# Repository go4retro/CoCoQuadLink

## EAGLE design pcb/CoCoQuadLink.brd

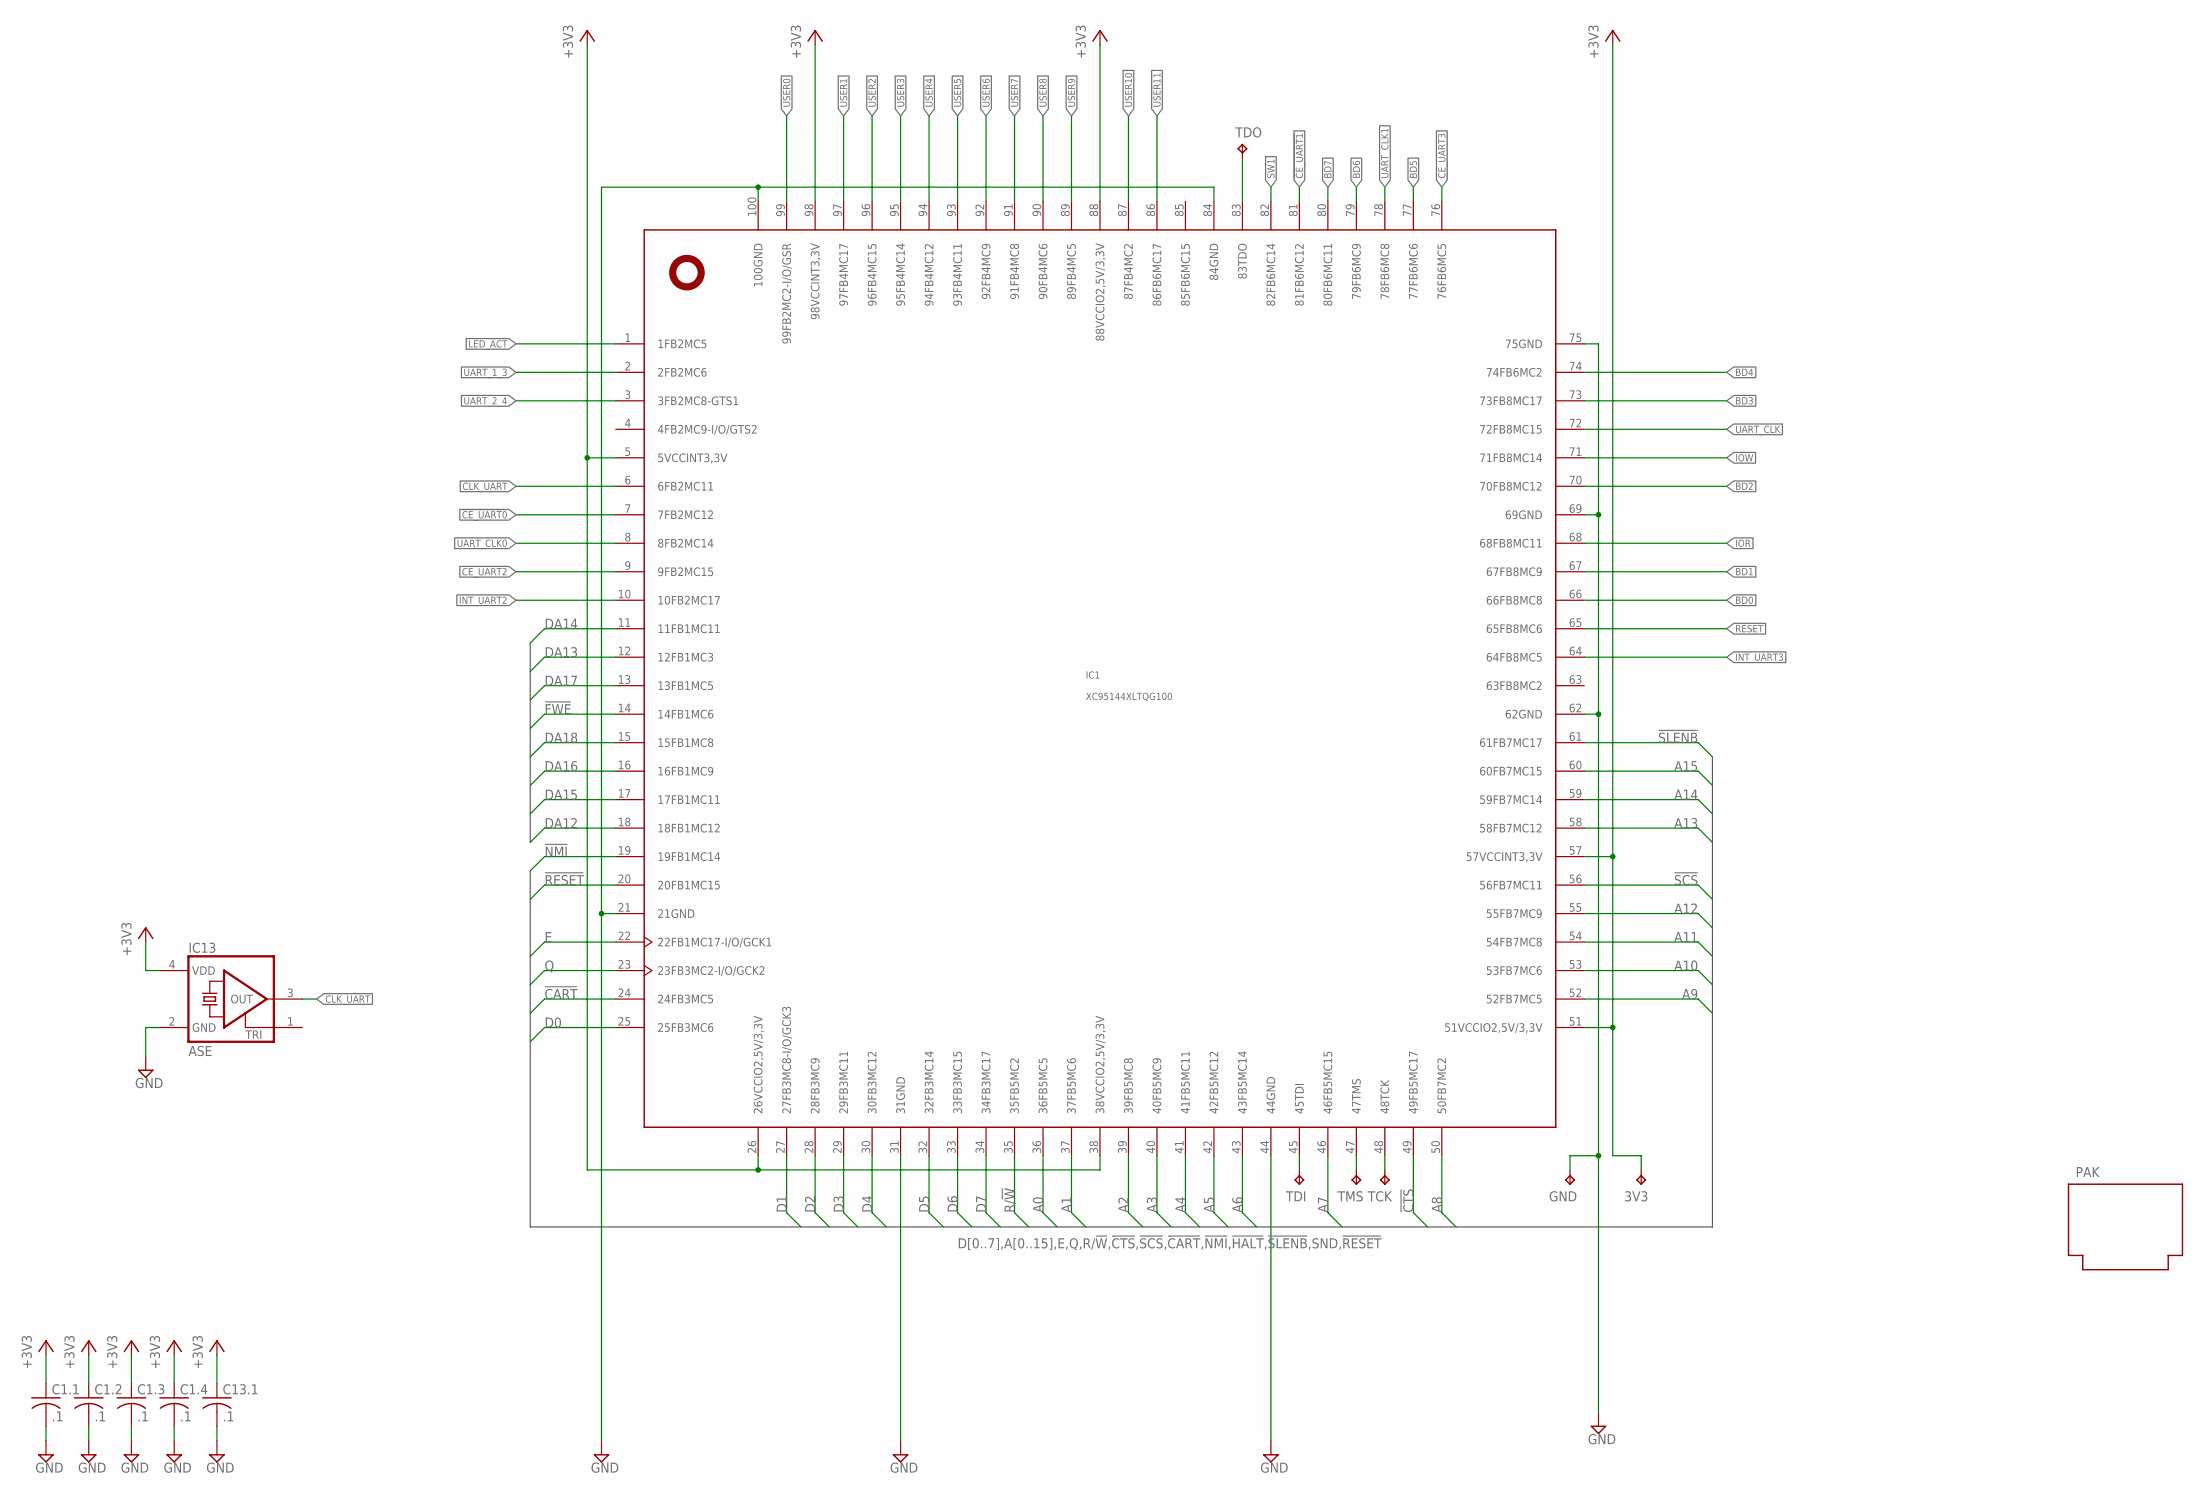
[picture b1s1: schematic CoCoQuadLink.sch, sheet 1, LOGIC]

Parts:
3V3: TPTP10R; TP10R
C1.1, C1.2, C1.3, C1.4, C13.1: .1; C0402
GND: TPTP10R; TP10R
IC1: XC95144XLTQG100; TQFP100
IC13: ASE
PAK: PROGRAM_PAK
TCK: TPTP10R; TP10R
TDI: TPTP10R; TP10R
TDO: TPTP10R; TP10R
TMS: TPTP10R; TP10R

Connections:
!CART: IC1.24 (24FB3MC5); also elsewhere on the board
!CE_UART0: IC1.7 (7FB2MC12); also elsewhere on the board
!CE_UART1: IC1.81 (81FB6MC12); also elsewhere on the board
!CTS: IC1.49 (49FB5MC17); also elsewhere on the board
!FWE: IC1.14 (14FB1MC6); also elsewhere on the board
!NMI: IC1.19 (19FB1MC14); also elsewhere on the board
!RESET: IC1.20 (20FB1MC15); also elsewhere on the board
!SCS: IC1.56 (56FB7MC11); also elsewhere on the board
!SLENB: IC1.61 (61FB7MC17); also elsewhere on the board
+3V3: 3V3.TP, C1.1.1, C1.2.1, C1.3.1, C1.4.1, C13.1.1, IC1.5 (5VCCINT3,3V), IC1.26 (26VCCIO2,5V/3,3V), IC1.38 (38VCCIO2,5V/3,3V), IC1.51 (51VCCIO2,5V/3,3V), IC1.57 (57VCCINT3,3V), IC1.88 (88VCCIO2,5V/3,3V), IC1.98 (98VCCINT3,3V), IC13.4 (VDD); also elsewhere on the board
A0: IC1.36 (36FB5MC5); also elsewhere on the board
A1: IC1.37 (37FB5MC6); also elsewhere on the board
A2: IC1.39 (39FB5MC8); also elsewhere on the board
A3: IC1.40 (40FB5MC9); also elsewhere on the board
A4: IC1.41 (41FB5MC11); also elsewhere on the board
A5: IC1.42 (42FB5MC12); also elsewhere on the board
A6: IC1.43 (43FB5MC14); also elsewhere on the board
A7: IC1.46 (46FB5MC15); also elsewhere on the board
A8: IC1.50 (50FB7MC2); also elsewhere on the board
A9: IC1.52 (52FB7MC5); also elsewhere on the board
A10: IC1.53 (53FB7MC6); also elsewhere on the board
A11: IC1.54 (54FB7MC8); also elsewhere on the board
A12: IC1.55 (55FB7MC9); also elsewhere on the board
A13: IC1.58 (58FB7MC12); also elsewhere on the board
A14: IC1.59 (59FB7MC14); also elsewhere on the board
A15: IC1.60 (60FB7MC15); also elsewhere on the board
BD0: IC1.66 (66FB8MC8); also elsewhere on the board
BD1: IC1.67 (67FB8MC9); also elsewhere on the board
BD2: IC1.70 (70FB8MC12); also elsewhere on the board
BD3: IC1.73 (73FB8MC17); also elsewhere on the board
BD4: IC1.74 (74FB6MC2); also elsewhere on the board
BD5: IC1.77 (77FB6MC6); also elsewhere on the board
BD6: IC1.79 (79FB6MC9); also elsewhere on the board
BD7: IC1.80 (80FB6MC11); also elsewhere on the board
CE_UART2: IC1.9 (9FB2MC15); also elsewhere on the board
CE_UART3: IC1.76 (76FB6MC5); also elsewhere on the board
CLK_UART: IC1.6 (6FB2MC11), IC13.3 (OUT)
D0: IC1.25 (25FB3MC6); also elsewhere on the board
D1: IC1.27 (27FB3MC8-I/O/GCK3); also elsewhere on the board
D2: IC1.28 (28FB3MC9); also elsewhere on the board
D3: IC1.29 (29FB3MC11); also elsewhere on the board
D4: IC1.30 (30FB3MC12); also elsewhere on the board
D5: IC1.32 (32FB3MC14); also elsewhere on the board
D6: IC1.33 (33FB3MC15); also elsewhere on the board
D7: IC1.34 (34FB3MC17); also elsewhere on the board
DA12: IC1.18 (18FB1MC12); also elsewhere on the board
DA13: IC1.12 (12FB1MC3); also elsewhere on the board
DA14: IC1.11 (11FB1MC11); also elsewhere on the board
DA15: IC1.17 (17FB1MC11); also elsewhere on the board
DA16: IC1.16 (16FB1MC9); also elsewhere on the board
DA17: IC1.13 (13FB1MC5); also elsewhere on the board
DA18: IC1.15 (15FB1MC8); also elsewhere on the board
E: IC1.22 (22FB1MC17-I/O/GCK1); also elsewhere on the board
GND: C1.1.2, C1.2.2, C1.3.2, C1.4.2, C13.1.2, GND.TP, IC1.21 (21GND), IC1.31 (31GND), IC1.44 (44GND), IC1.62 (62GND), IC1.69 (69GND), IC1.75 (75GND), IC1.84 (84GND), IC1.100 (100GND), IC13.2 (GND); also elsewhere on the board
INT_UART2: IC1.10 (10FB2MC17); also elsewhere on the board
INT_UART3: IC1.64 (64FB8MC5); also elsewhere on the board
IOR: IC1.68 (68FB8MC11); also elsewhere on the board
IOW: IC1.71 (71FB8MC14); also elsewhere on the board
LED_ACT: IC1.1 (1FB2MC5); also elsewhere on the board
unnamed: IC1.45 (45TDI), TDI.TP
unnamed: IC1.47 (47TMS), TMS.TP
unnamed: IC1.48 (48TCK), TCK.TP
unnamed: IC1.83 (83TDO), TDO.TP
Q: IC1.23 (23FB3MC2-I/O/GCK2); also elsewhere on the board
R/!W: IC1.35 (35FB5MC2); also elsewhere on the board
RESET: IC1.65 (65FB8MC6); also elsewhere on the board
SW1: IC1.82 (82FB6MC14); also elsewhere on the board
UART_1_3: IC1.2 (2FB2MC6); also elsewhere on the board
UART_2_4: IC1.3 (3FB2MC8-GTS1); also elsewhere on the board
UART_CLK: IC1.72 (72FB8MC15); also elsewhere on the board
UART_CLK0: IC1.8 (8FB2MC14); also elsewhere on the board
UART_CLK1: IC1.78 (78FB6MC8); also elsewhere on the board
USER0: IC1.99 (99FB2MC2-I/O/GSR); also elsewhere on the board
USER1: IC1.97 (97FB4MC17); also elsewhere on the board
USER2: IC1.96 (96FB4MC15); also elsewhere on the board
USER3: IC1.95 (95FB4MC14); also elsewhere on the board
USER4: IC1.94 (94FB4MC12); also elsewhere on the board
USER5: IC1.93 (93FB4MC11); also elsewhere on the board
USER6: IC1.92 (92FB4MC9); also elsewhere on the board
USER7: IC1.91 (91FB4MC8); also elsewhere on the board
USER8: IC1.90 (90FB4MC6); also elsewhere on the board
USER9: IC1.89 (89FB4MC5); also elsewhere on the board
USER10: IC1.87 (87FB4MC2); also elsewhere on the board
USER11: IC1.86 (86FB6MC17); also elsewhere on the board

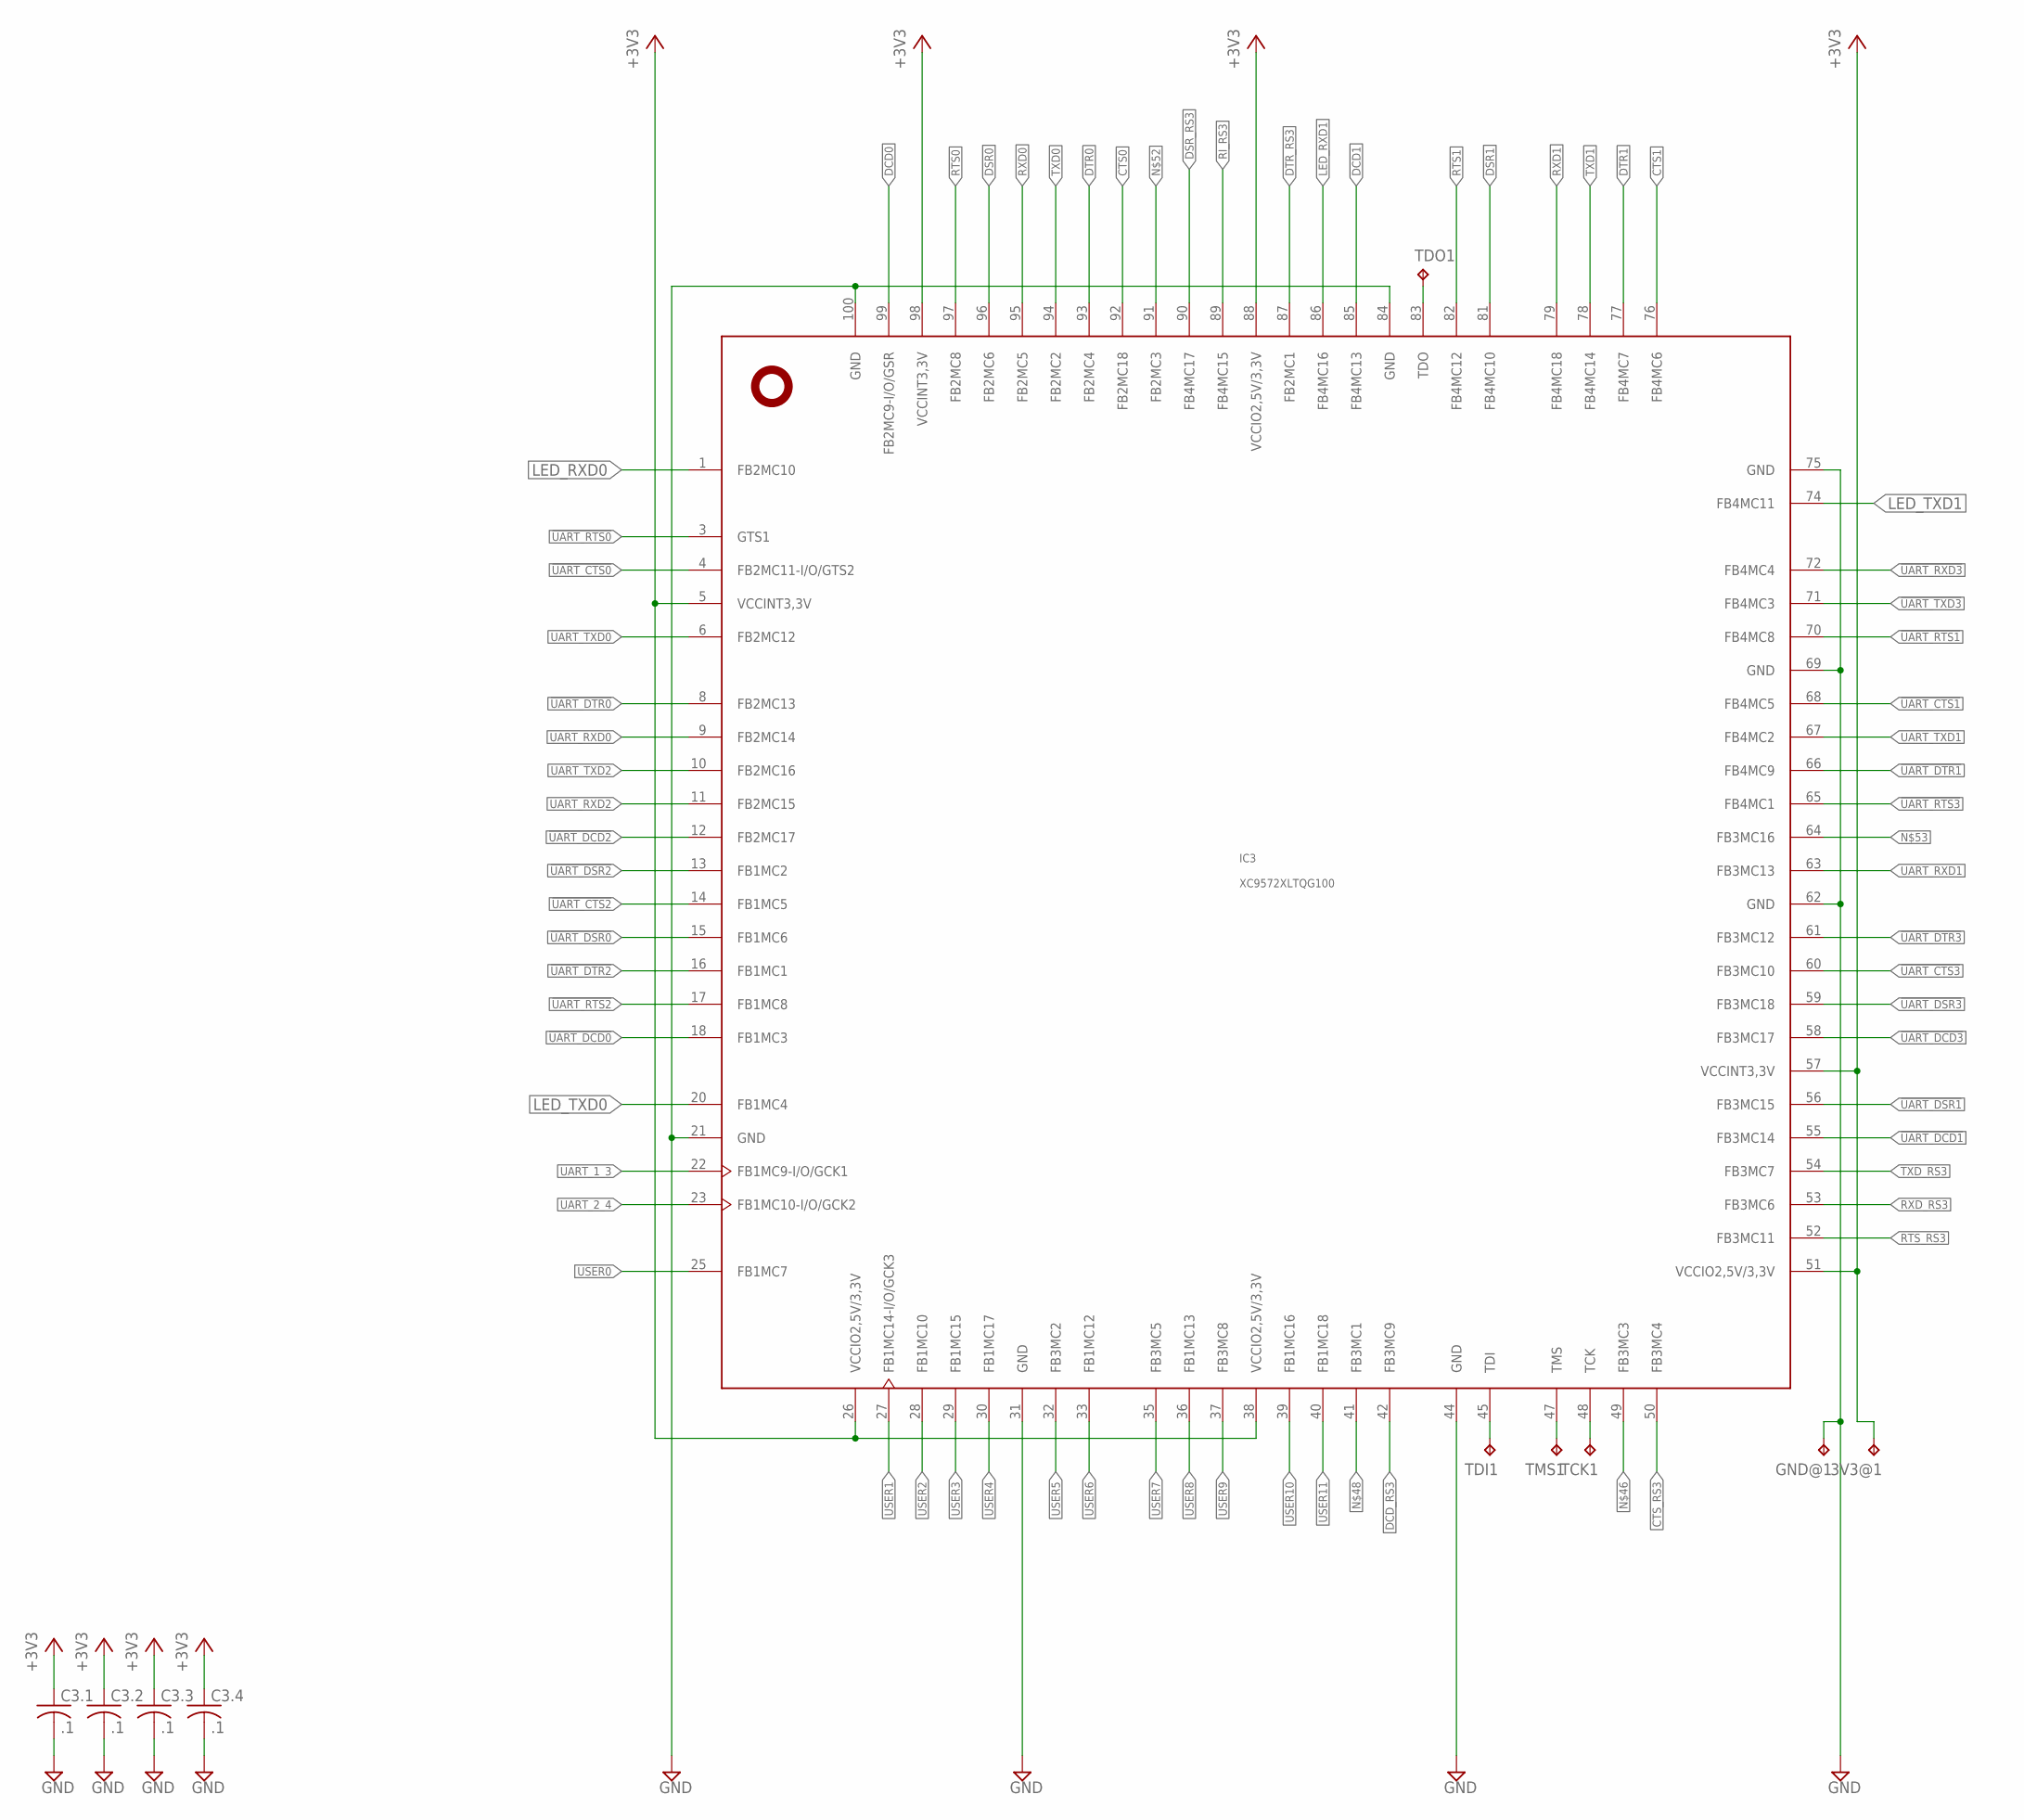
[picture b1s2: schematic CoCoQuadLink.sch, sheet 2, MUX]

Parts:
3V3@1: TPTP10R; TP10R
C3.1, C3.2, C3.3, C3.4: .1; C0402
GND@1: TPTP10R; TP10R
IC3: XC9572XLTQG100; TQFP100
TCK1: TPTP10R; TP10R
TDI1: TPTP10R; TP10R
TDO1: TPTP10R; TP10R
TMS1: TPTP10R; TP10R

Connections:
!CTS0: IC3.92 (FB2MC18); also elsewhere on the board
!CTS1: IC3.76 (FB4MC6); also elsewhere on the board
!DCD0: IC3.99 (FB2MC9-I/O/GSR); also elsewhere on the board
!DCD1: IC3.85 (FB4MC13); also elsewhere on the board
!DSR0: IC3.96 (FB2MC6); also elsewhere on the board
!DSR1: IC3.81 (FB4MC10); also elsewhere on the board
!DTR0: IC3.93 (FB2MC4); also elsewhere on the board
!DTR1: IC3.77 (FB4MC7); also elsewhere on the board
!RTS0: IC3.97 (FB2MC8); also elsewhere on the board
!RTS1: IC3.82 (FB4MC12); also elsewhere on the board
!UART_CTS0: IC3.4 (FB2MC11-I/O/GTS2); also elsewhere on the board
!UART_CTS1: IC3.68 (FB4MC5); also elsewhere on the board
!UART_CTS2: IC3.14 (FB1MC5); also elsewhere on the board
!UART_CTS3: IC3.60 (FB3MC10); also elsewhere on the board
!UART_DCD0: IC3.18 (FB1MC3); also elsewhere on the board
!UART_DCD1: IC3.55 (FB3MC14); also elsewhere on the board
!UART_DCD2: IC3.12 (FB2MC17); also elsewhere on the board
!UART_DCD3: IC3.58 (FB3MC17); also elsewhere on the board
!UART_DSR0: IC3.15 (FB1MC6); also elsewhere on the board
!UART_DSR1: IC3.56 (FB3MC15); also elsewhere on the board
!UART_DSR2: IC3.13 (FB1MC2); also elsewhere on the board
!UART_DSR3: IC3.59 (FB3MC18); also elsewhere on the board
!UART_DTR0: IC3.8 (FB2MC13); also elsewhere on the board
!UART_DTR1: IC3.66 (FB4MC9); also elsewhere on the board
!UART_DTR2: IC3.16 (FB1MC1); also elsewhere on the board
!UART_DTR3: IC3.61 (FB3MC12); also elsewhere on the board
!UART_RTS0: IC3.3 (GTS1); also elsewhere on the board
!UART_RTS1: IC3.70 (FB4MC8); also elsewhere on the board
!UART_RTS2: IC3.17 (FB1MC8); also elsewhere on the board
!UART_RTS3: IC3.65 (FB4MC1); also elsewhere on the board
!UART_RXD3: IC3.72 (FB4MC4); also elsewhere on the board
!UART_TXD3: IC3.71 (FB4MC3); also elsewhere on the board
+3V3: 3V3@1.TP, C3.1.1, C3.2.1, C3.3.1, C3.4.1, IC3.5 (VCCINT3,3V), IC3.26 (VCCIO2,5V/3,3V), IC3.38 (VCCIO2,5V/3,3V), IC3.51 (VCCIO2,5V/3,3V), IC3.57 (VCCINT3,3V), IC3.88 (VCCIO2,5V/3,3V), IC3.98 (VCCINT3,3V); also elsewhere on the board
CTS_RS3: IC3.50 (FB3MC4); also elsewhere on the board
DCD_RS3: IC3.42 (FB3MC9); also elsewhere on the board
DSR_RS3: IC3.90 (FB4MC17); also elsewhere on the board
DTR_RS3: IC3.87 (FB2MC1); also elsewhere on the board
GND: C3.1.2, C3.2.2, C3.3.2, C3.4.2, GND@1.TP, IC3.21 (GND), IC3.31 (GND), IC3.44 (GND), IC3.62 (GND), IC3.69 (GND), IC3.75 (GND), IC3.84 (GND), IC3.100 (GND); also elsewhere on the board
LED_RXD0: IC3.1 (FB2MC10); also elsewhere on the board
LED_RXD1: IC3.86 (FB4MC16); also elsewhere on the board
LED_TXD0: IC3.20 (FB1MC4); also elsewhere on the board
LED_TXD1: IC3.74 (FB4MC11); also elsewhere on the board
unnamed: IC3.83 (TDO), TDO1.TP
unnamed: IC3.45 (TDI), TDI1.TP
unnamed: IC3.47 (TMS), TMS1.TP
unnamed: IC3.48 (TCK), TCK1.TP
unnamed 143: IC3.49 (FB3MC3); also elsewhere on the board
unnamed 144: IC3.41 (FB3MC1); also elsewhere on the board
unnamed 145: IC3.91 (FB2MC3); also elsewhere on the board
unnamed 146: IC3.64 (FB3MC16); also elsewhere on the board
RI_RS3: IC3.89 (FB4MC15); also elsewhere on the board
RTS_RS3: IC3.52 (FB3MC11); also elsewhere on the board
RXD0: IC3.95 (FB2MC5); also elsewhere on the board
RXD1: IC3.79 (FB4MC18); also elsewhere on the board
RXD_RS3: IC3.53 (FB3MC6); also elsewhere on the board
TXD0: IC3.94 (FB2MC2); also elsewhere on the board
TXD1: IC3.78 (FB4MC14); also elsewhere on the board
TXD_RS3: IC3.54 (FB3MC7); also elsewhere on the board
UART_1_3: IC3.22 (FB1MC9-I/O/GCK1); also elsewhere on the board
UART_2_4: IC3.23 (FB1MC10-I/O/GCK2); also elsewhere on the board
UART_RXD0: IC3.9 (FB2MC14); also elsewhere on the board
UART_RXD1: IC3.63 (FB3MC13); also elsewhere on the board
UART_RXD2: IC3.11 (FB2MC15); also elsewhere on the board
UART_TXD0: IC3.6 (FB2MC12); also elsewhere on the board
UART_TXD1: IC3.67 (FB4MC2); also elsewhere on the board
UART_TXD2: IC3.10 (FB2MC16); also elsewhere on the board
USER0: IC3.25 (FB1MC7); also elsewhere on the board
USER1: IC3.27 (FB1MC14-I/O/GCK3); also elsewhere on the board
USER2: IC3.28 (FB1MC10); also elsewhere on the board
USER3: IC3.29 (FB1MC15); also elsewhere on the board
USER4: IC3.30 (FB1MC17); also elsewhere on the board
USER5: IC3.32 (FB3MC2); also elsewhere on the board
USER6: IC3.33 (FB1MC12); also elsewhere on the board
USER7: IC3.35 (FB3MC5); also elsewhere on the board
USER8: IC3.36 (FB1MC13); also elsewhere on the board
USER9: IC3.37 (FB3MC8); also elsewhere on the board
USER10: IC3.39 (FB1MC16); also elsewhere on the board
USER11: IC3.40 (FB1MC18); also elsewhere on the board

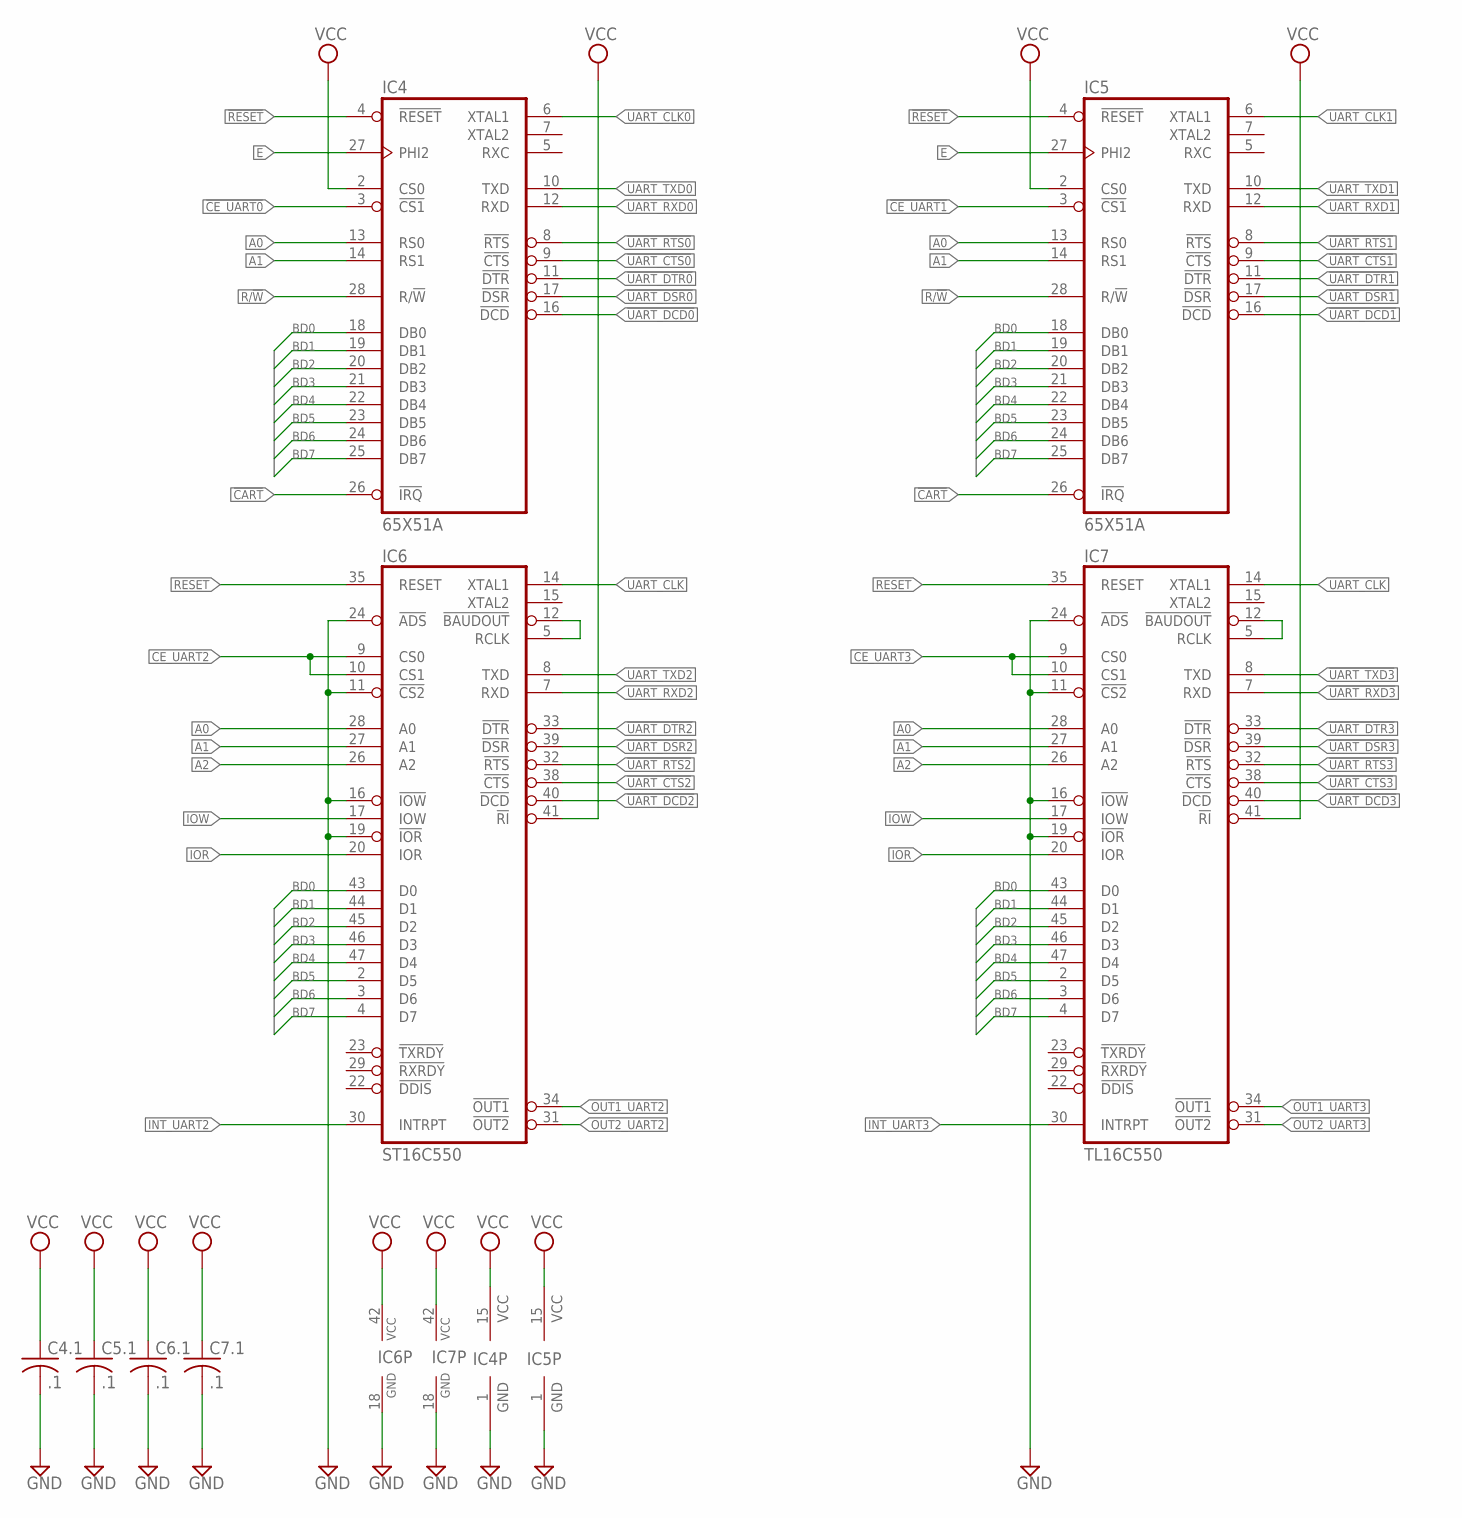
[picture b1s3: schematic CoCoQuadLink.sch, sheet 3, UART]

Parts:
C4.1, C5.1, C6.1, C7.1: .1; C0402
IC4, IC5: 65X51A; DIL28-ROUNDPAD
IC6: ST16C550; LQFP48
IC7: TL16C550; LQFP48

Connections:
!CART: IC4.26 (!IRQ), IC5.26 (!IRQ); also elsewhere on the board
!CE_UART0: IC4.3 (!CS1); also elsewhere on the board
!CE_UART1: IC5.3 (!CS1); also elsewhere on the board
!RESET: IC4.4 (!RESET), IC5.4 (!RESET); also elsewhere on the board
!UART_CTS0: IC4.9 (!CTS); also elsewhere on the board
!UART_CTS1: IC5.9 (!CTS); also elsewhere on the board
!UART_CTS2: IC6.38 (!CTS); also elsewhere on the board
!UART_CTS3: IC7.38 (!CTS); also elsewhere on the board
!UART_DCD0: IC4.16 (!DCD); also elsewhere on the board
!UART_DCD1: IC5.16 (!DCD); also elsewhere on the board
!UART_DCD2: IC6.40 (!DCD); also elsewhere on the board
!UART_DCD3: IC7.40 (!DCD); also elsewhere on the board
!UART_DSR0: IC4.17 (!DSR); also elsewhere on the board
!UART_DSR1: IC5.17 (!DSR); also elsewhere on the board
!UART_DSR2: IC6.39 (!DSR); also elsewhere on the board
!UART_DSR3: IC7.39 (!DSR); also elsewhere on the board
!UART_DTR0: IC4.11 (!DTR); also elsewhere on the board
!UART_DTR1: IC5.11 (!DTR); also elsewhere on the board
!UART_DTR2: IC6.33 (!DTR); also elsewhere on the board
!UART_DTR3: IC7.33 (!DTR); also elsewhere on the board
!UART_RTS0: IC4.8 (!RTS); also elsewhere on the board
!UART_RTS1: IC5.8 (!RTS); also elsewhere on the board
!UART_RTS2: IC6.32 (!RTS); also elsewhere on the board
!UART_RTS3: IC7.32 (!RTS); also elsewhere on the board
!UART_RXD3: IC7.7 (RXD); also elsewhere on the board
!UART_TXD3: IC7.8 (TXD); also elsewhere on the board
A0: IC4.13 (RS0), IC5.13 (RS0), IC6.28 (A0), IC7.28 (A0); also elsewhere on the board
A1: IC4.14 (RS1), IC5.14 (RS1), IC6.27 (A1), IC7.27 (A1); also elsewhere on the board
A2: IC6.26 (A2), IC7.26 (A2); also elsewhere on the board
BD0: IC4.18 (DB0), IC5.18 (DB0), IC6.43 (D0), IC7.43 (D0); also elsewhere on the board
BD1: IC4.19 (DB1), IC5.19 (DB1), IC6.44 (D1), IC7.44 (D1); also elsewhere on the board
BD2: IC4.20 (DB2), IC5.20 (DB2), IC6.45 (D2), IC7.45 (D2); also elsewhere on the board
BD3: IC4.21 (DB3), IC5.21 (DB3), IC6.46 (D3), IC7.46 (D3); also elsewhere on the board
BD4: IC4.22 (DB4), IC5.22 (DB4), IC6.47 (D4), IC7.47 (D4); also elsewhere on the board
BD5: IC4.23 (DB5), IC5.23 (DB5), IC6.2 (D5), IC7.2 (D5); also elsewhere on the board
BD6: IC4.24 (DB6), IC5.24 (DB6), IC6.3 (D6), IC7.3 (D6); also elsewhere on the board
BD7: IC4.25 (DB7), IC5.25 (DB7), IC6.4 (D7), IC7.4 (D7); also elsewhere on the board
CE_UART2: IC6.9 (CS0), IC6.10 (CS1); also elsewhere on the board
CE_UART3: IC7.9 (CS0), IC7.10 (CS1); also elsewhere on the board
E: IC4.27 (PHI2), IC5.27 (PHI2); also elsewhere on the board
GND: C4.1.2, C5.1.2, C6.1.2, C7.1.2, IC4.1 (GND), IC5.1 (GND), IC6.11 (!CS2), IC6.16 (!IOW), IC6.18 (GND), IC6.19 (!IOR), IC6.24 (!ADS), IC7.11 (!CS2), IC7.16 (!IOW), IC7.18 (GND), IC7.19 (!IOR), IC7.24 (!ADS); also elsewhere on the board
INT_UART2: IC6.30 (INTRPT); also elsewhere on the board
INT_UART3: IC7.30 (INTRPT); also elsewhere on the board
IOR: IC6.20 (IOR), IC7.20 (IOR); also elsewhere on the board
IOW: IC6.17 (IOW), IC7.17 (IOW); also elsewhere on the board
unnamed: IC6.5 (RCLK), IC6.12 (!BAUDOUT)
unnamed: IC7.5 (RCLK), IC7.12 (!BAUDOUT)
OUT1_UART2: IC6.34 (!OUT1)
OUT1_UART3: IC7.34 (!OUT1)
OUT2_UART2: IC6.31 (!OUT2)
OUT2_UART3: IC7.31 (!OUT2)
R/!W: IC4.28 (R/!W), IC5.28 (R/!W); also elsewhere on the board
RESET: IC6.35 (RESET), IC7.35 (RESET); also elsewhere on the board
UART_CLK: IC6.14 (XTAL1), IC7.14 (XTAL1); also elsewhere on the board
UART_CLK0: IC4.6 (XTAL1); also elsewhere on the board
UART_CLK1: IC5.6 (XTAL1); also elsewhere on the board
UART_RXD0: IC4.12 (RXD); also elsewhere on the board
UART_RXD1: IC5.12 (RXD); also elsewhere on the board
UART_RXD2: IC6.7 (RXD); also elsewhere on the board
UART_TXD0: IC4.10 (TXD); also elsewhere on the board
UART_TXD1: IC5.10 (TXD); also elsewhere on the board
UART_TXD2: IC6.8 (TXD); also elsewhere on the board
VCC: C4.1.1, C5.1.1, C6.1.1, C7.1.1, IC4.2 (CS0), IC4.15 (VCC), IC5.2 (CS0), IC5.15 (VCC), IC6.41 (!RI), IC6.42 (VCC), IC7.41 (!RI), IC7.42 (VCC); also elsewhere on the board

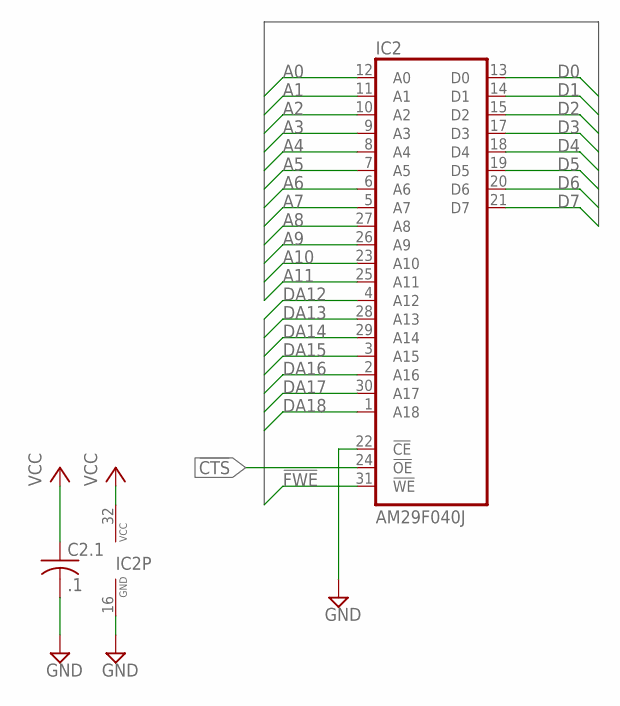
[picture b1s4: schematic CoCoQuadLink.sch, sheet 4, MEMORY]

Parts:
C2.1: .1; C0402
IC2: AM29F040J; PLCC32R

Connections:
!CTS: IC2.24 (!OE); also elsewhere on the board
!FWE: IC2.31 (!WE); also elsewhere on the board
A0: IC2.12 (A0); also elsewhere on the board
A1: IC2.11 (A1); also elsewhere on the board
A2: IC2.10 (A2); also elsewhere on the board
A3: IC2.9 (A3); also elsewhere on the board
A4: IC2.8 (A4); also elsewhere on the board
A5: IC2.7 (A5); also elsewhere on the board
A6: IC2.6 (A6); also elsewhere on the board
A7: IC2.5 (A7); also elsewhere on the board
A8: IC2.27 (A8); also elsewhere on the board
A9: IC2.26 (A9); also elsewhere on the board
A10: IC2.23 (A10); also elsewhere on the board
A11: IC2.25 (A11); also elsewhere on the board
D0: IC2.13 (D0); also elsewhere on the board
D1: IC2.14 (D1); also elsewhere on the board
D2: IC2.15 (D2); also elsewhere on the board
D3: IC2.17 (D3); also elsewhere on the board
D4: IC2.18 (D4); also elsewhere on the board
D5: IC2.19 (D5); also elsewhere on the board
D6: IC2.20 (D6); also elsewhere on the board
D7: IC2.21 (D7); also elsewhere on the board
DA12: IC2.4 (A12); also elsewhere on the board
DA13: IC2.28 (A13); also elsewhere on the board
DA14: IC2.29 (A14); also elsewhere on the board
DA15: IC2.3 (A15); also elsewhere on the board
DA16: IC2.2 (A16); also elsewhere on the board
DA17: IC2.30 (A17); also elsewhere on the board
DA18: IC2.1 (A18); also elsewhere on the board
GND: C2.1.2, IC2.16 (GND), IC2.22 (!CE); also elsewhere on the board
VCC: C2.1.1, IC2.32 (VCC); also elsewhere on the board

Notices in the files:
parts and their libraries:
SparkFun: Licensing: CC v3.0 Share-Alike You are welcome to use this library for commercial purposes.
